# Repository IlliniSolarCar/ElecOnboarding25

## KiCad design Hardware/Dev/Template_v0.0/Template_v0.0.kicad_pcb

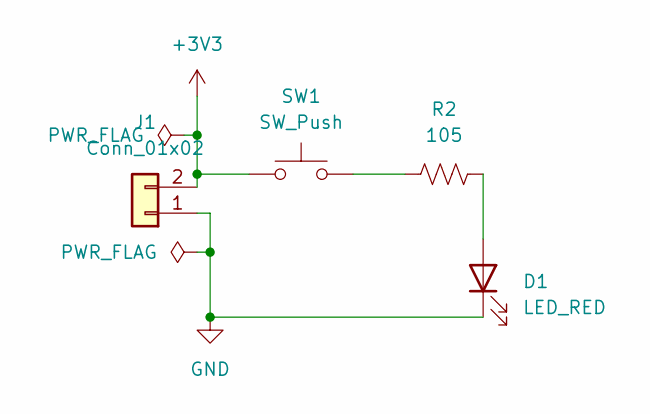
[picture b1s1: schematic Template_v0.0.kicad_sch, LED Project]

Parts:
D1: LED_RED; LED_0603_Symbol_on_F.SilkS
J1: Conn_01x02; Molex_KK-254_AE-6410-02A_1x02_P2.54mm_Vertical; MPN 022272021
R2: 105; R_0603_1608Metric_Pad0.98x0.95mm_HandSolder
SW1: SW_Push; SW_DIP_SPSTx01_Slide_6.7x4.1mm_W8.61mm_P2.54mm_LowProfile; MPN 1825910-6

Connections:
+3V3: J1.2, SW1.1
GND: D1.1 (K), J1.1
unnamed: D1.2 (A), R2.2
unnamed: R2.1, SW1.2

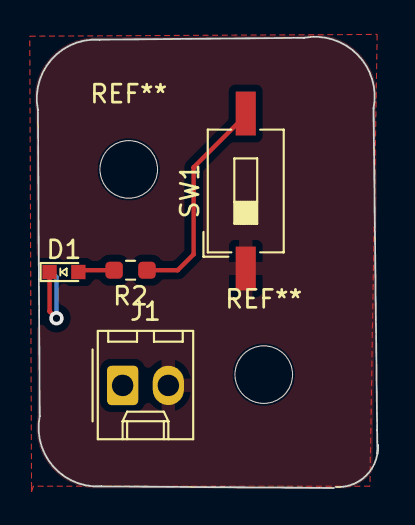
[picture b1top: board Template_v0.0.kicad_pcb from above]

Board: 2 copper layers, 18.9 x 25.1 mm, 4 parts (0 on the bottom side), 4 nets.

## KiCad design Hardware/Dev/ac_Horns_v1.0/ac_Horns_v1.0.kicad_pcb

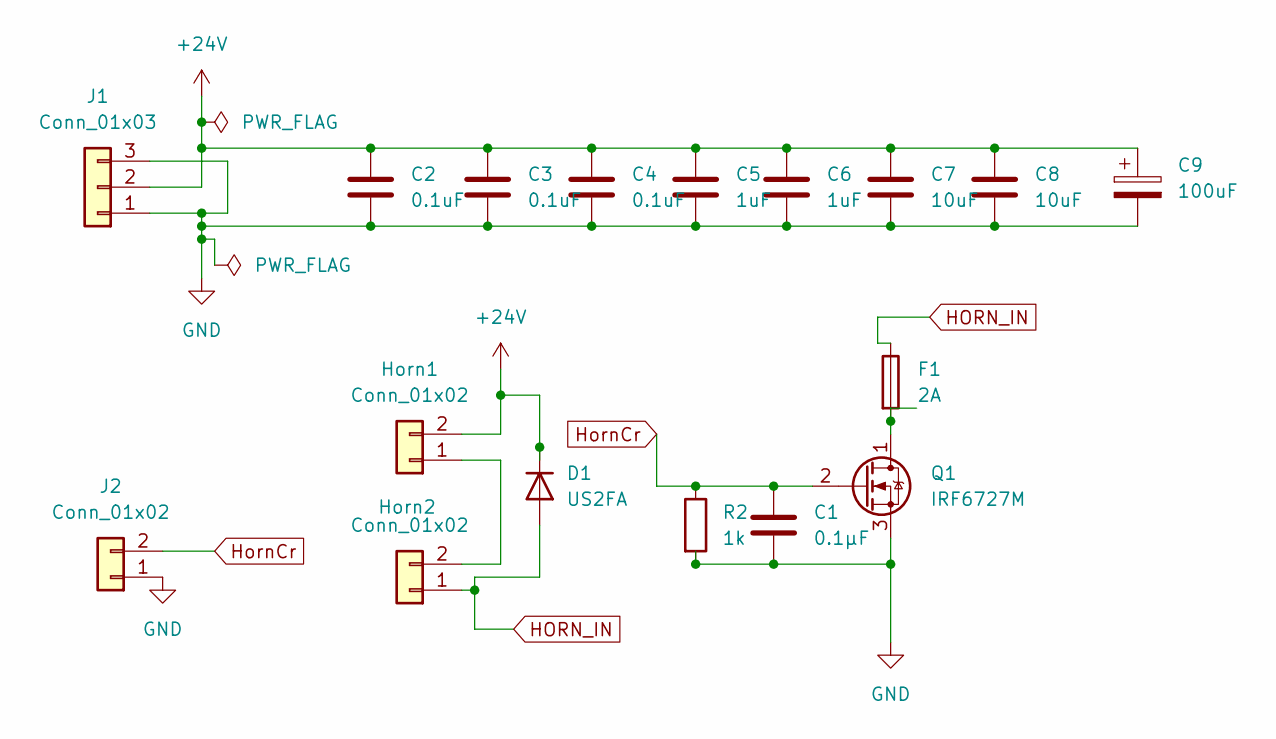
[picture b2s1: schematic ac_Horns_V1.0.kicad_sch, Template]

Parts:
C1: 0.1μF; C_0603_1608Metric
C2, C3, C4: 0.1uF; C_0603_1608Metric
C5, C6: 1uF; C_0603_1608Metric
C7, C8: 10uF; C_0603_1608Metric
C9: 100uF; C_0603_1608Metric
D1: US2FA; D_A-405_P10.16mm_Horizontal
F1: 2A; Fuse_0603_1608Metric
Horn1, Horn2: Conn_01x02; Molex_Micro-Fit_3.0_43650-0200_1x02_P3.00mm_Horizontal
J1: Conn_01x03; Molex_Micro-Fit_3.0_43650-0300_1x03_P3.00mm_Horizontal
J2: Conn_01x02; Molex_Micro-Fit_3.0_43650-0200_1x02_P3.00mm_Horizontal
Q1: IRF6727M; DirectFET_MX
R2: 1k; R_0612_1632Metric

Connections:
+24V: C2.1, C3.1, C4.1, C5.1, C6.1, C7.1, C8.1, C9.1, D1.1 (K), Horn1.2, J1.2
GND: C1.2, C2.2, C3.2, C4.2, C5.2, C6.2, C7.2, C8.2, C9.2, J1.1, J1.3, J2.1, Q1.3 (S), R2.2
HORN_IN: D1.2 (A), F1.1, Horn2.1
HornCr: C1.1, J2.2, Q1.2 (G), R2.1
unnamed: Horn1.1, Horn2.2
unnamed: F1.2, Q1.1 (D)

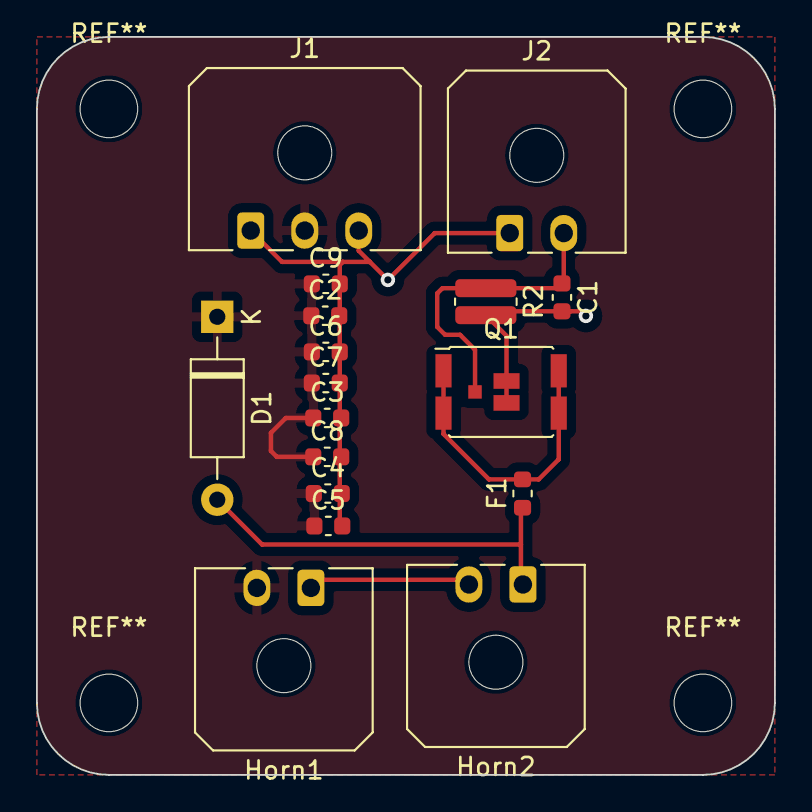
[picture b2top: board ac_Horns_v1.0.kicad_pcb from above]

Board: 2 copper layers, 41.0 x 41.0 mm, 17 parts (0 on the bottom side), 6 nets.

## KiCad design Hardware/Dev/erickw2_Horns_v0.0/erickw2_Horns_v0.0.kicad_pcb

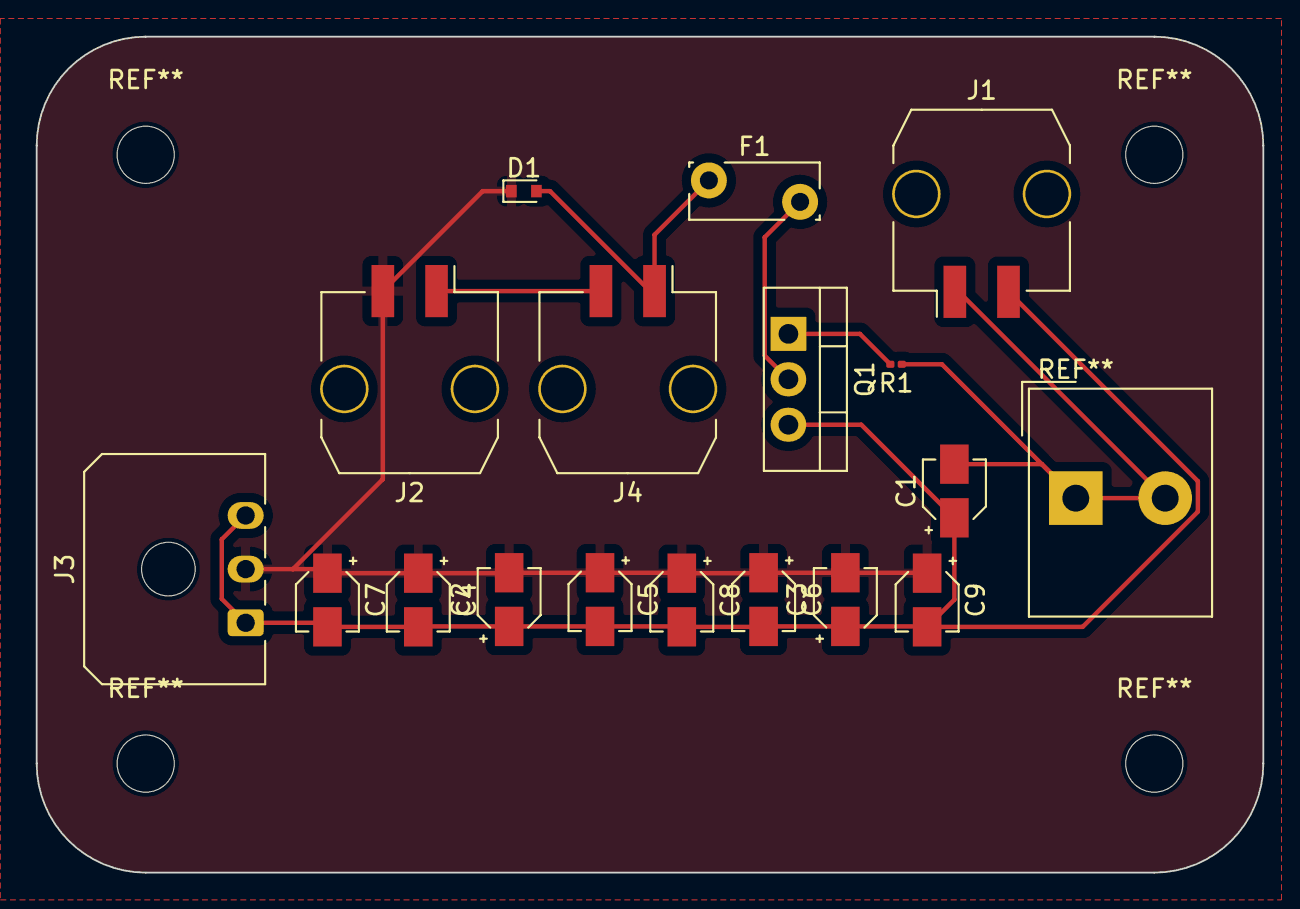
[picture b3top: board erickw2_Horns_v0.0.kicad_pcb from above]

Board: 2 copper layers, 68.6 x 46.7 mm, 17 parts (0 on the bottom side), 7 nets.

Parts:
C1, C2, C3: 1 microFarad; CP_Elec_3x5.3
C4, C5, C6: 0.1 microF; CP_Elec_3x5.3
C7, C8: 10 microF; CP_Elec_3x5.3
C9: 100 microF; CP_Elec_3x5.3
D1: 1N4148WT; D_SOD-523
F1: 2A; Fuse_Bourns_MF-RG300
J1, J2, J4: Conn_01x02; Molex_Micro-Fit_3.0_43650-0210_1x02-1MP_P3.00mm_Horizontal
J3: Conn_01x03; Molex_Micro-Fit_3.0_43650-0300_1x03_P3.00mm_Horizontal
Q1: IRLZ44N; TO-220-3_Vertical
R1: 1 KOhm; R_0201_0603Metric

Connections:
+24V: C2.2, C3.2, C4.1, C5.1, C6.1, C7.1, C8.1, C9.1, D1.1 (K), J2.2, J3.2
/Horn Control: C1.2, J1.1, R1.1
GND: C1.1, C2.1, C3.1, C4.2, C5.2, C6.2, C7.2, C8.2, C9.2, J1.2, J3.1, J3.3, Q1.3 (S)
unnamed: D1.2 (A), F1.1, J4.1
unnamed: J2.1, J4.2
unnamed: F1.2, Q1.2 (D)
unnamed: Q1.1 (G), R1.2

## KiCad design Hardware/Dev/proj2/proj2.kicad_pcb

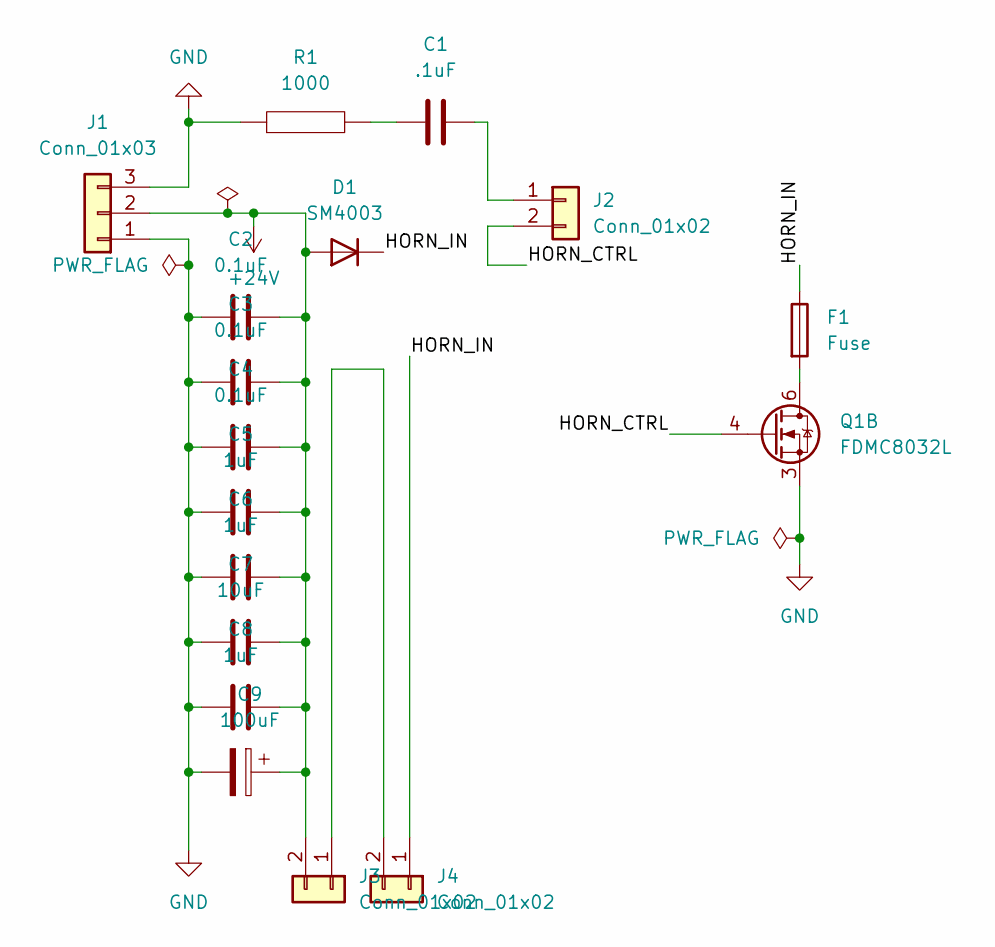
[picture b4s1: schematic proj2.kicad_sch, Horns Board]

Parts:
C1: .1uF
C2, C3, C4: 0.1uF
C5, C6, C8: 1uF
C7: 10uF
C9: 100uF
D1: SM4003; D_MELF
F1: Fuse
J1: Conn_01x03
J2, J3, J4: Conn_01x02
Q1: FDMC8032L; Fairchild_DualPower33-6_3x3mm
R1: 1000

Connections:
+24V: C2.2, C3.2, C4.2, C5.2, C6.2, C7.2, C8.2, C9.1, D1.2 (A), J1.2, J3.2
/HORN_CTRL: J2.2, Q1.4 (G2)
/HORN_IN: D1.1 (K), F1.1, J4.1
GND: C2.1, C3.1, C4.1, C5.1, C6.1, C7.1, C8.1, C9.2, J1.1, J1.3, Q1.3 (S2), R1.1
unnamed: C1.1, R1.2
unnamed: C1.2, J2.1
unnamed: J3.1, J4.2
unnamed: F1.2, Q1.6 (D2)

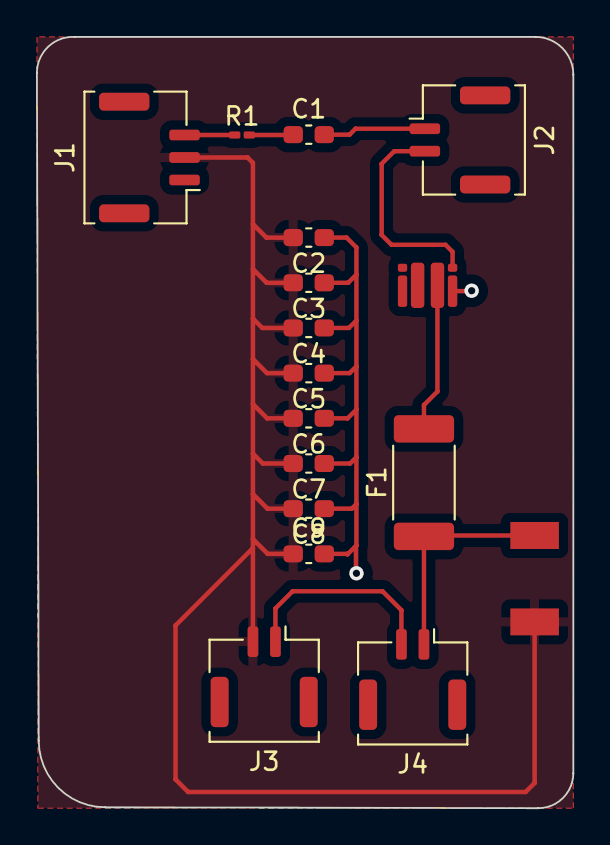
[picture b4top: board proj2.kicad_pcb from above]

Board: 2 copper layers, 29.8 x 42.8 mm, 17 parts (0 on the bottom side), 8 nets.

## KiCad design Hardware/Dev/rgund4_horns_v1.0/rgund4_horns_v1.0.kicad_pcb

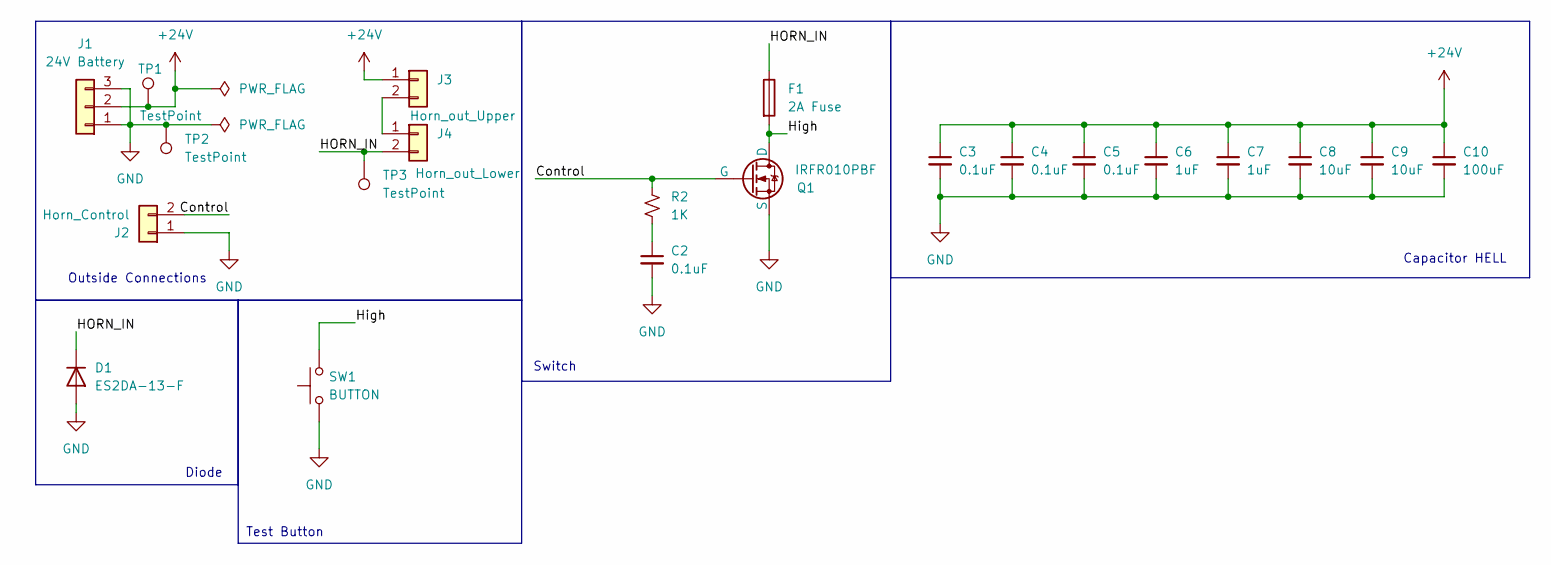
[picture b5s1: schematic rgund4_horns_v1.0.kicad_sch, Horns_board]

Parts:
C2, C3, C4, C5: 0.1uF; C_Elec_3x5.4
C6, C7: 1uF; C_Elec_3x5.4
C8, C9: 10uF; C_Elec_3x5.4
C10: 100uF; CAP_YX_6P3X11_RUB(100uF)
D1: ES2DA-13-F; CR_SMA_DIO(Diode)
F1: 2A Fuse; C2_BEL(Fuse)
J1: 24V Battery; Molex_Micro-Fit_3.0_43650-0300_1x03_P3.00mm_Horizontal
J2: Horn_Control; Molex_Micro-Fit_3.0_43650-0200_1x02_P3.00mm_Horizontal
J3: Horn_out_Upper; Molex_Micro-Fit_3.0_43650-0200_1x02_P3.00mm_Horizontal
J4: Horn_out_Lower; Molex_Micro-Fit_3.0_43650-0200_1x02_P3.00mm_Horizontal
Q1: IRFR010PBF; DPAK_R010_VIS(MOSFET)
R2: 1K; R_0402_1005Metric_Pad0.72x0.64mm_HandSolder
SW1: BUTTON; SW_Push_1P1T_NO_Vertical_Wuerth_434133025816
TP1, TP2, TP3: TestPoint; TestPoint_Pad_1.0x1.0mm

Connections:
+24V: C3.1, C4.1, C5.1, C6.1, C7.1, C8.1, C9.1, C10.1, J1.2, J3.1, TP1.1
/Control: J2.2, Q1.2 (G), R2.2
/HORN_IN: D1.1 (K), F1.1, J4.2, TP3.1
/High: F1.2, Q1.1 (D), SW1.2
GND: C2.2, C3.2, C4.2, C5.2, C6.2, C7.2, C8.2, C9.2, C10.2, D1.2 (A), J1.1, J1.3, J2.1, Q1.3 (S), SW1.1, TP2.1
unnamed: C2.1, R2.1
unnamed: J3.2, J4.1

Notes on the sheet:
Switch
Outside Connections
Test Button
Diode
Capacitor HELL

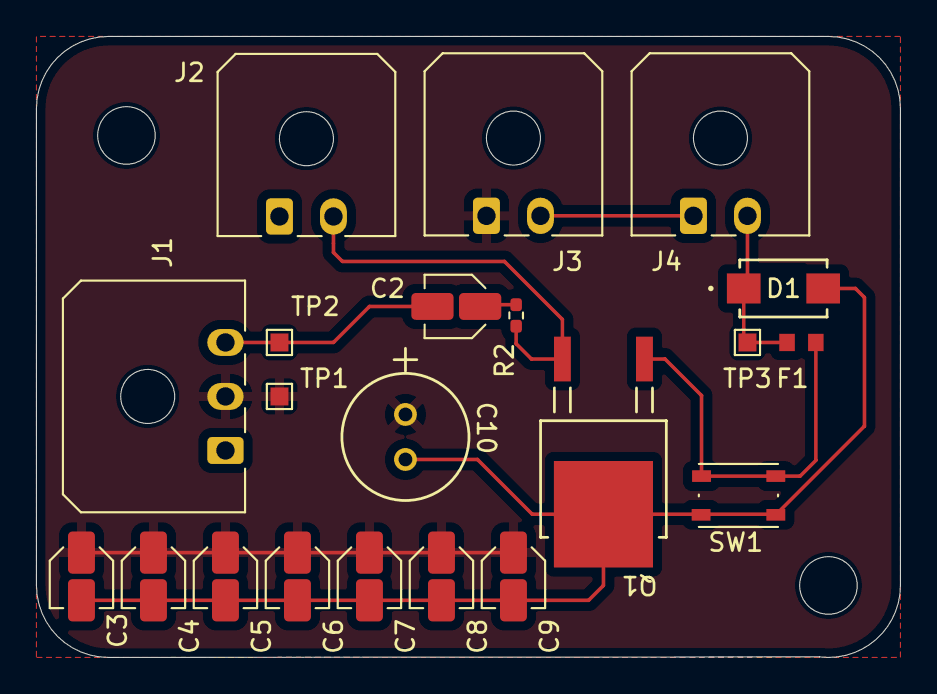
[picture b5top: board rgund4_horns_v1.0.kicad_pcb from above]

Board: 2 copper layers, 48.0 x 34.5 mm, 21 parts (0 on the bottom side), 7 nets.

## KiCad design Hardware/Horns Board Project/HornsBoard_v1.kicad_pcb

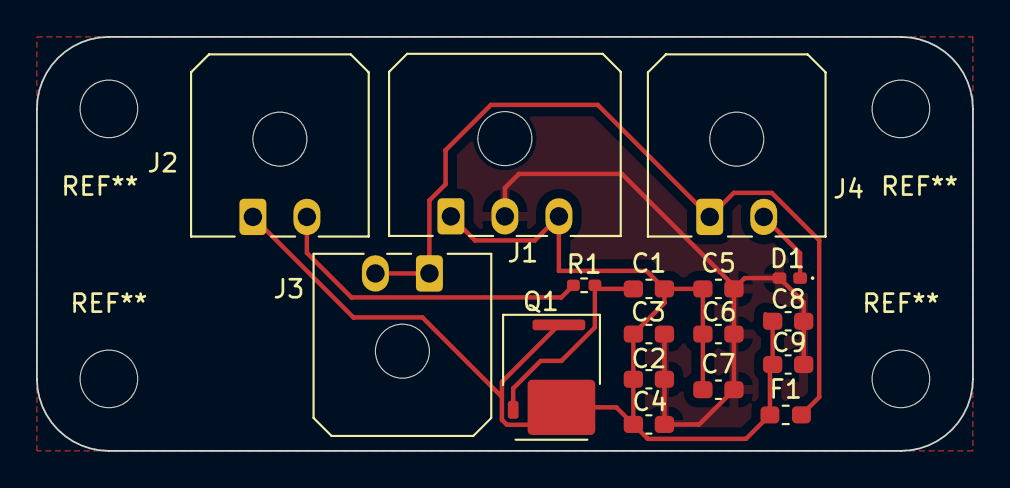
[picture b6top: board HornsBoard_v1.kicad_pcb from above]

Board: 2 copper layers, 52.0 x 23.0 mm, 17 parts (0 on the bottom side), 6 nets.

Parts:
C1, C5, C6, C7: 0.1uF; C_0603_1608Metric_Pad1.08x0.95mm_HandSolder
C2: 100uF; C_0603_1608Metric_Pad1.08x0.95mm_HandSolder
C3, C4: 1uF; C_0603_1608Metric_Pad1.08x0.95mm_HandSolder
C8: 10uf; C_0603_1608Metric_Pad1.08x0.95mm_HandSolder
C9: 10uF; C_0603_1608Metric_Pad1.08x0.95mm_HandSolder
D1: D_Small; D_0402_1005Metric_Pad0.77x0.64mm_HandSolder
F1: 2A; Fuse_0603_1608Metric_Pad1.05x0.95mm_HandSolder
J1: Conn_01x03; Molex_Micro-Fit_3.0_43650-0300_1x03_P3.00mm_Horizontal
J2, J3, J4: Conn_01x02; Molex_Micro-Fit_3.0_43650-0200_1x02_P3.00mm_Horizontal
Q1: Q_NMOS_DGS; GaN_Systems_GaNPX-3_5x6.6mm_Drain2.93x0.6mm
R1: 1000; R_0402_1005Metric_Pad0.72x0.64mm_HandSolder

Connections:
+24V: C2.1, C3.2, C4.2, C5.2, C6.2, C7.2, C8.2, C9.2, D1.2 (A), J1.2
/HORN_CTRL: J2.2, R1.1
/HORN_IN: F1.2, J3.1, J3.2, J4.1
GND: C1.2, C2.2, C3.1, C4.1, C5.1, C6.1, C7.1, C8.1, C9.1, F1.1, J1.1, J1.3, J2.1, Q1.1 (D), Q1.3 (S)
unnamed: D1.1 (K), J4.2
unnamed: C1.1, Q1.2 (G), R1.2
